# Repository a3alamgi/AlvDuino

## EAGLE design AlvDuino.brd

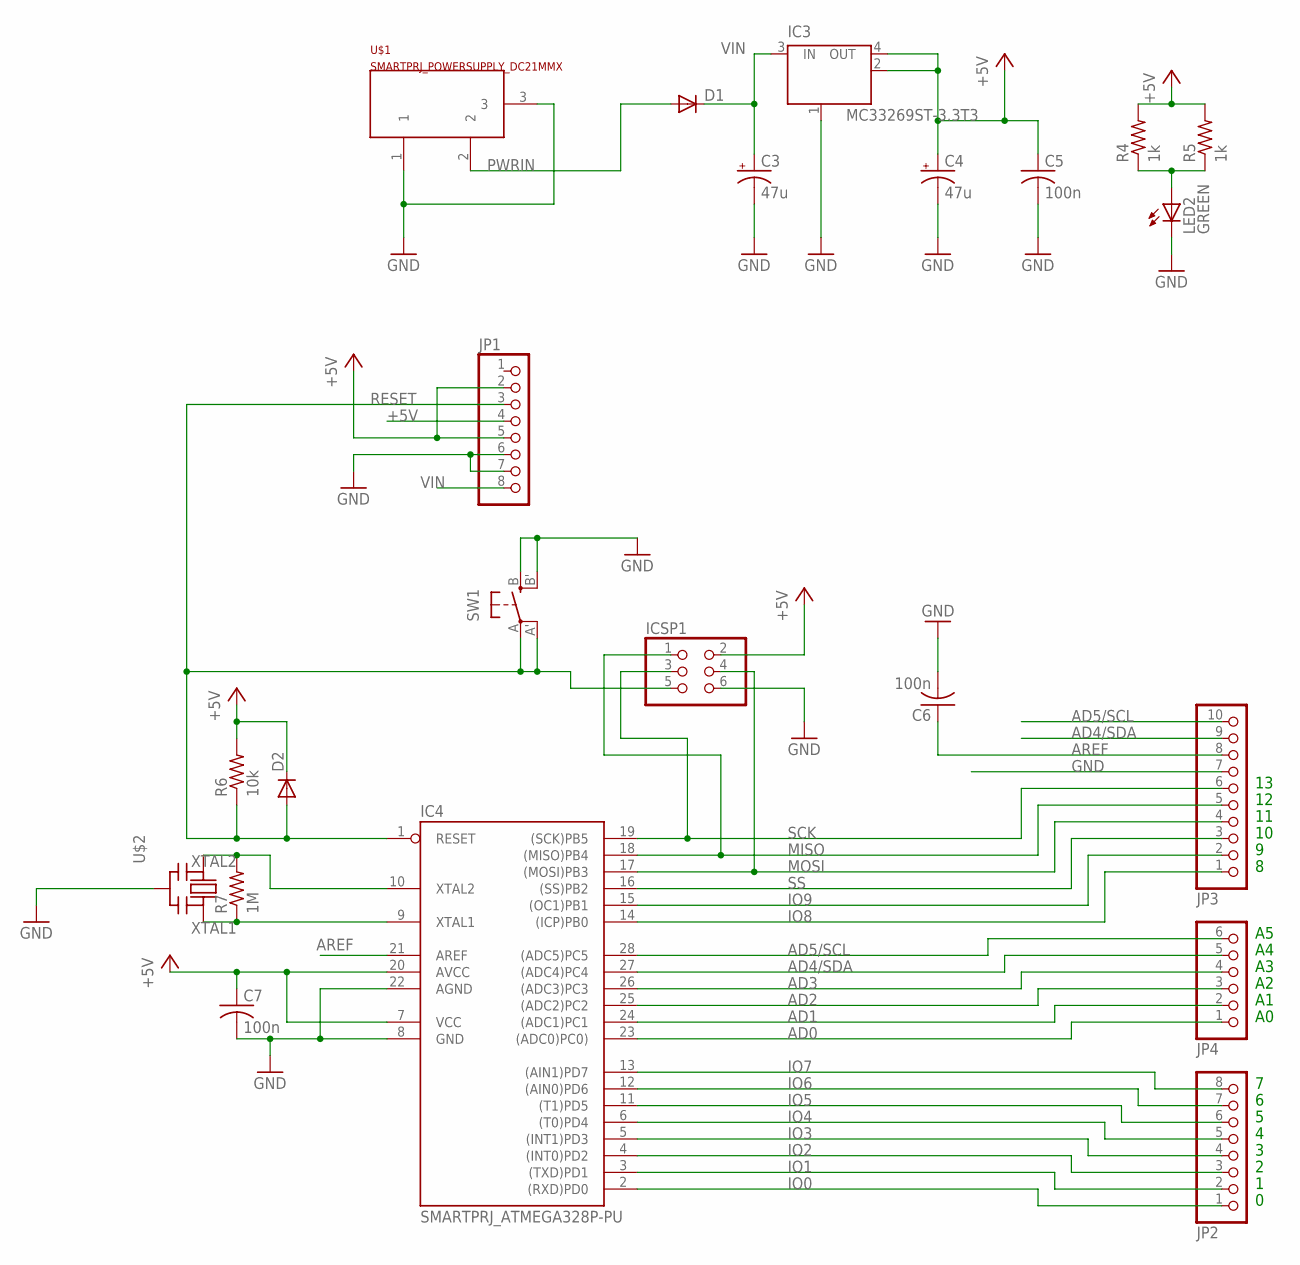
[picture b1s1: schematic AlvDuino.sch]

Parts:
C3, C4: 47u; PANASONIC_D
C5, C6, C7: 100n; C1206
D1, D2: DIODE-DO214AA; DO214AA
IC3: MC33269ST-3.3T3; SOT223
IC4: SMARTPRJ_ATMEGA328P-PU; SMARTPRJ_DIL28-3
ICSP1: PINHD-2X3; 2X03
JP1, JP2: PINHD-1X8; 1X08
JP3: PINHD-1X10; 1X10
JP4: PINHD-1X6; 1X06
LED2: GREEN; CHIPLED_1206
R4, R5: 1k; R1206
R6: 10k; R1206
R7: 1M; R1206
SW1: SPST_TACT-EVQQ2; EVQ-Q2
U$1: SMARTPRJ_POWERSUPPLY_DC21MMX; SMARTPRJ_POWERSUPPLY_DC-21MM
U$2: CERMOSCILL-THM; CERM_OSC

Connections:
+5V: C4.+, C5.1, C7.1, D2.C, IC3.2 (OUT), IC3.4 (OUT), IC4.7 (VCC), IC4.20 (AVCC), ICSP1.2, JP1.2, JP1.4, JP1.5, R4.2, R5.2, R6.2
AD0: IC4.23 ((ADC0)PC0)), JP4.1
AD1: IC4.24 ((ADC1)PC1), JP4.2
AD2: IC4.25 ((ADC2)PC2), JP4.3
AD3: IC4.26 ((ADC3)PC3), JP4.4
AD4/SDA: IC4.27 ((ADC4)PC4), JP3.9, JP4.5
AD5/SCL: IC4.28 ((ADC5)PC5), JP3.10, JP4.6
AREF: C6.1, IC4.21 (AREF), JP3.8
GND: C3.-, C4.-, C5.2, C6.2, C7.2, IC3.1 (GND/ADJ), IC4.8 (GND), IC4.22 (AGND), ICSP1.6, JP1.6, JP1.7, JP3.7, LED2.C, SW1.B (S), SW1.B' (S1), U$1.1, U$1.3, U$2.P$2 (GND)
IO0: IC4.2 ((RXD)PD0), JP2.1
IO1: IC4.3 ((TXD)PD1), JP2.2
IO2: IC4.4 ((INT0)PD2), JP2.3
IO3: IC4.5 ((INT1)PD3), JP2.4
IO4: IC4.6 ((T0)PD4), JP2.5
IO5: IC4.11 ((T1)PD5), JP2.6
IO6: IC4.12 ((AIN0)PD6), JP2.7
IO7: IC4.13 ((AIN1)PD7), JP2.8
IO8: IC4.14 ((ICP)PB0), JP3.1
IO9: IC4.15 ((OC1)PB1), JP3.2
MISO: IC4.18 ((MISO)PB4), ICSP1.1, JP3.5
MOSI: IC4.17 ((MOSI)PB3), ICSP1.4, JP3.4
unnamed: LED2.A, R4.1, R5.1
PWRIN: D1.A, U$1.2
RESET: D2.A, IC4.1 (RESET), ICSP1.5, JP1.3, R6.1, SW1.A, SW1.A' (P1)
SCK: IC4.19 ((SCK)PB5), ICSP1.3, JP3.6
SS: IC4.16 ((SS)PB2), JP3.3
VIN: C3.+, D1.C, IC3.3 (IN), JP1.8
XTAL1: IC4.9 (XTAL1), R7.1, U$2.P$3 (OUT)
XTAL2: IC4.10 (XTAL2), R7.2, U$2.P$1 (IN)

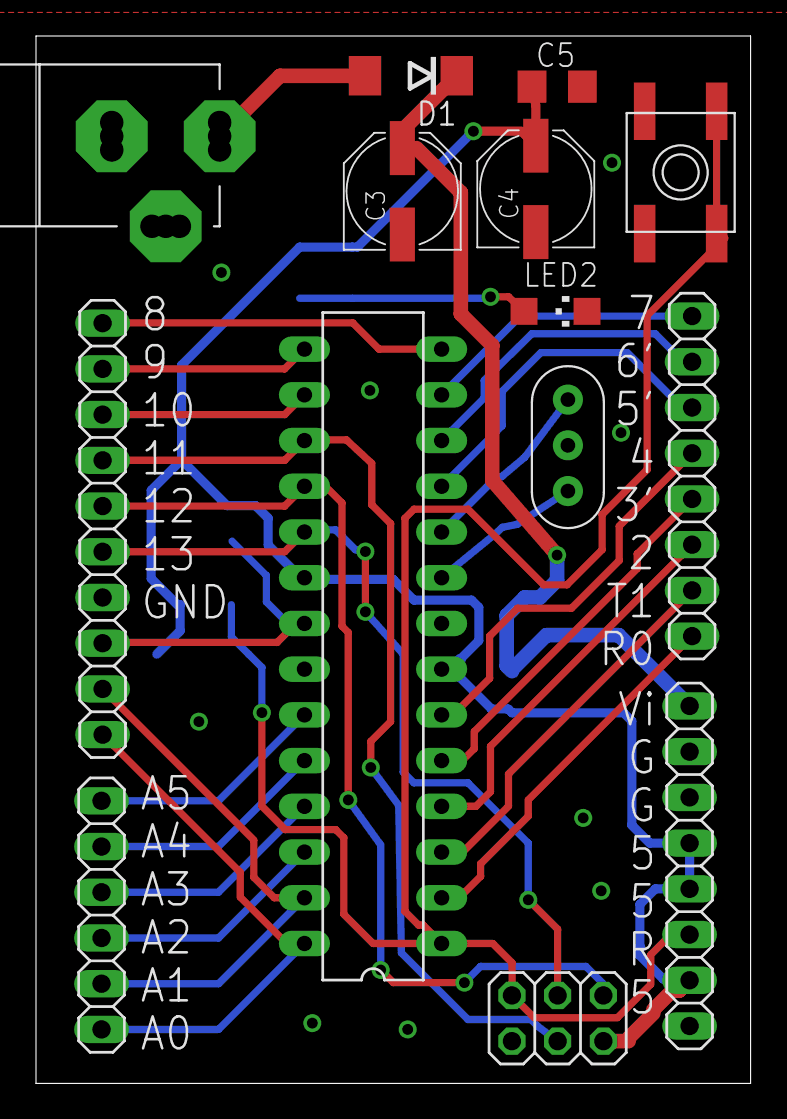
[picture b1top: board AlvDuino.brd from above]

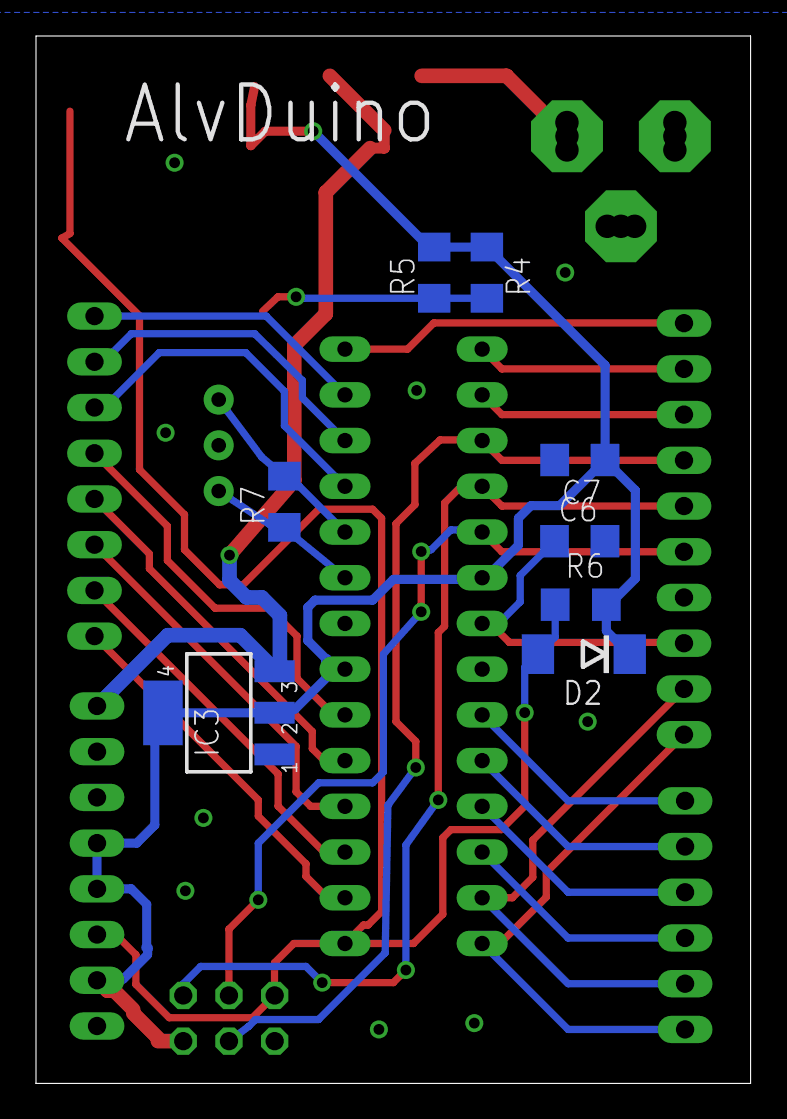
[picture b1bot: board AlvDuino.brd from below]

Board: 2 copper layers, 39.7 x 58.2 mm, 22 parts (8 on the bottom side), 29 nets.

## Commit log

2014-05-09 Fixed Figure
